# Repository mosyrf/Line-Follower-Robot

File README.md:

# Line-Follower-Robot
It was my first-year project as an electrical engineering student, to build a robot that could follow black or white lines. It wasn't a special line follower robot; it was designed to gain experience in project-based learning as a beginner.

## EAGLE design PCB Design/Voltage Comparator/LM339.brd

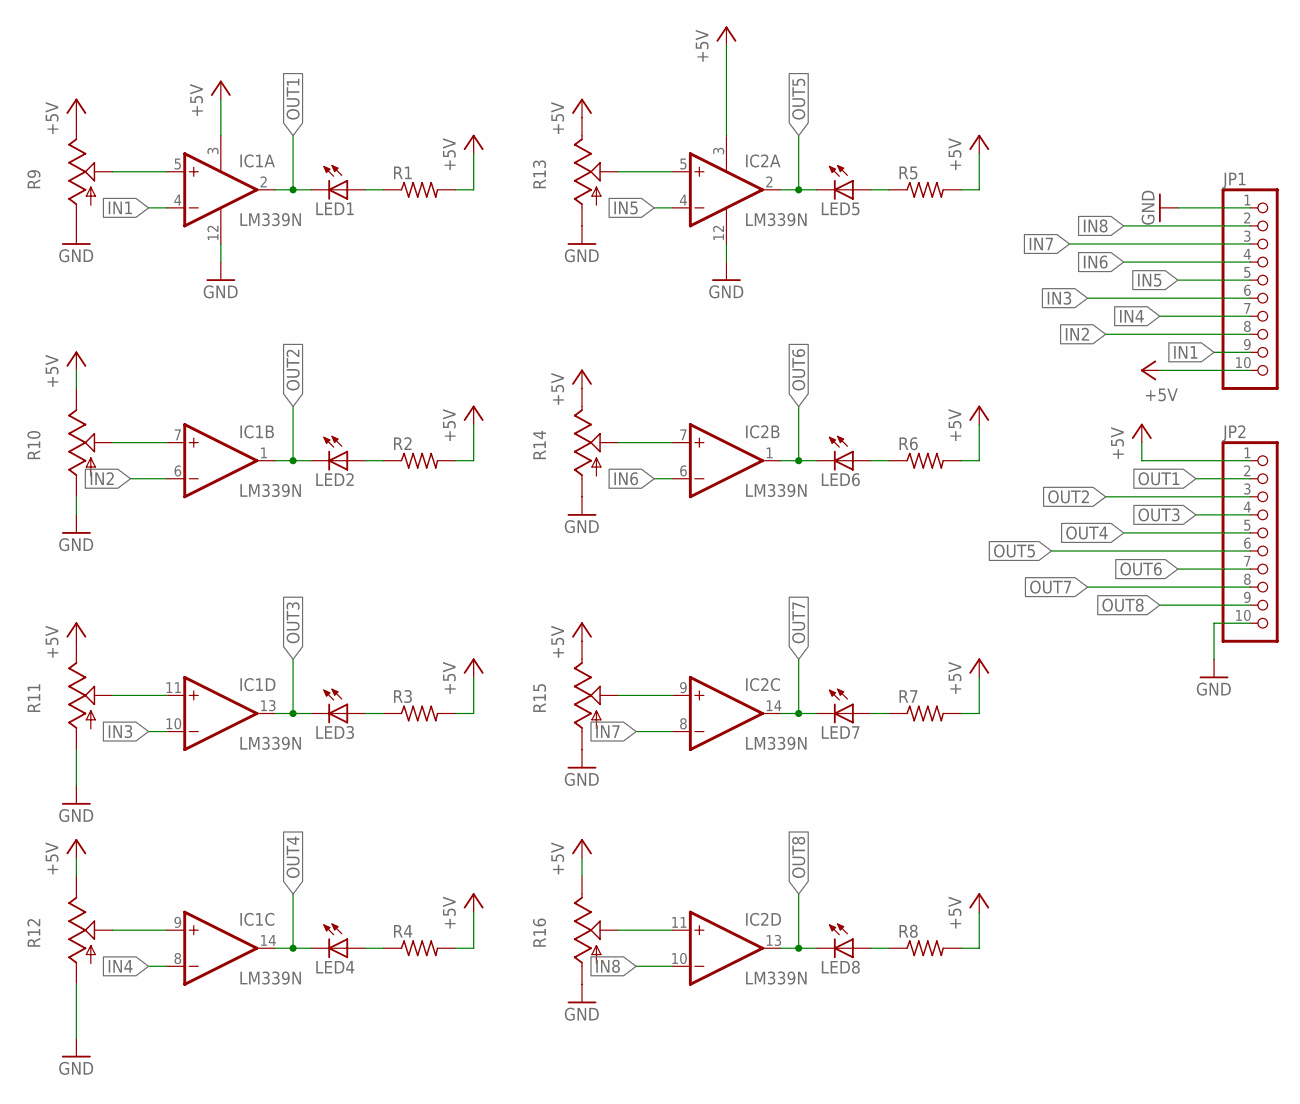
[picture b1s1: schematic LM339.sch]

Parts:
IC1, IC2: LM339N; DIL14
JP1, JP2: PINHD-1X10; 1X10
LED1, LED2, LED3, LED4, LED5, LED6, LED7, LED8: LED5MM
R1, R2, R3, R4, R5, R6, R7, R8: R-US_0204/7; 0204/7
R9, R10, R11, R12, R13, R14, R15, R16: TRIM_US-B25P; B25P

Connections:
+5V: IC1.3 (V+), IC2.3 (V+), JP1.10, JP2.1, R1.2, R2.2, R3.2, R4.2, R5.2, R6.2, R7.2, R8.2, R9.E, R10.E, R11.E, R12.E, R13.E, R14.E, R15.E, R16.E
GND: IC1.12 (GND), IC2.12 (GND), JP1.1, JP2.10, R9.A, R10.A, R11.A, R12.A, R13.A, R14.A, R15.A, R16.A
IN1: IC1.4 (-IN), JP1.9
IN2: IC1.6 (-IN), JP1.8
IN3: IC1.10 (-IN), JP1.6
IN4: IC1.8 (-IN), JP1.7
IN5: IC2.4 (-IN), JP1.5
IN6: IC2.6 (-IN), JP1.4
IN7: IC2.8 (-IN), JP1.3
IN8: IC2.10 (-IN), JP1.2
unnamed: LED2.A, R2.1
unnamed: LED1.A, R1.1
unnamed: LED3.A, R3.1
unnamed: LED4.A, R4.1
unnamed: LED5.A, R5.1
unnamed: LED6.A, R6.1
unnamed: LED7.A, R7.1
unnamed: LED8.A, R8.1
unnamed: IC1.11 (+IN), R11.S
unnamed: IC1.5 (+IN), R9.S
unnamed: IC1.7 (+IN), R10.S
unnamed: IC1.9 (+IN), R12.S
unnamed: IC2.9 (+IN), R15.S
unnamed: IC2.5 (+IN), R13.S
unnamed: IC2.7 (+IN), R14.S
unnamed: IC2.11 (+IN), R16.S
OUT1: IC1.2 (OUT), JP2.2, LED1.K (C)
OUT2: IC1.1 (OUT), JP2.3, LED2.K (C)
OUT3: IC1.13 (OUT), JP2.4, LED3.K (C)
OUT4: IC1.14 (OUT), JP2.5, LED4.K (C)
OUT5: IC2.2 (OUT), JP2.6, LED5.K (C)
OUT6: IC2.1 (OUT), JP2.7, LED6.K (C)
OUT7: IC2.14 (OUT), JP2.8, LED7.K (C)
OUT8: IC2.13 (OUT), JP2.9, LED8.K (C)

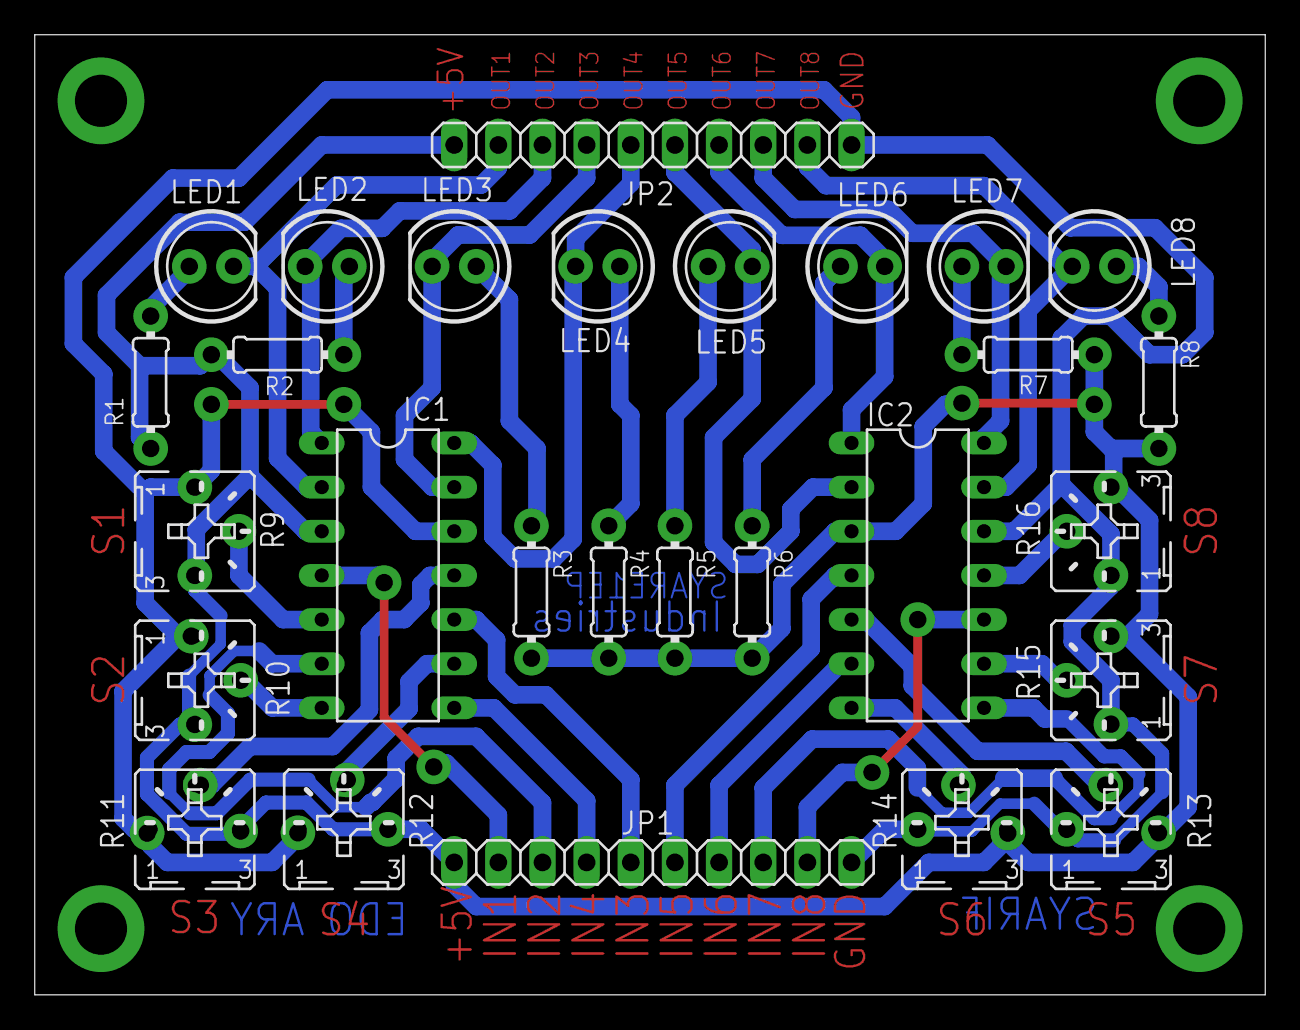
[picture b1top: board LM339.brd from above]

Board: 2 copper layers, 70.8 x 55.2 mm, 28 parts (0 on the bottom side), 34 nets.

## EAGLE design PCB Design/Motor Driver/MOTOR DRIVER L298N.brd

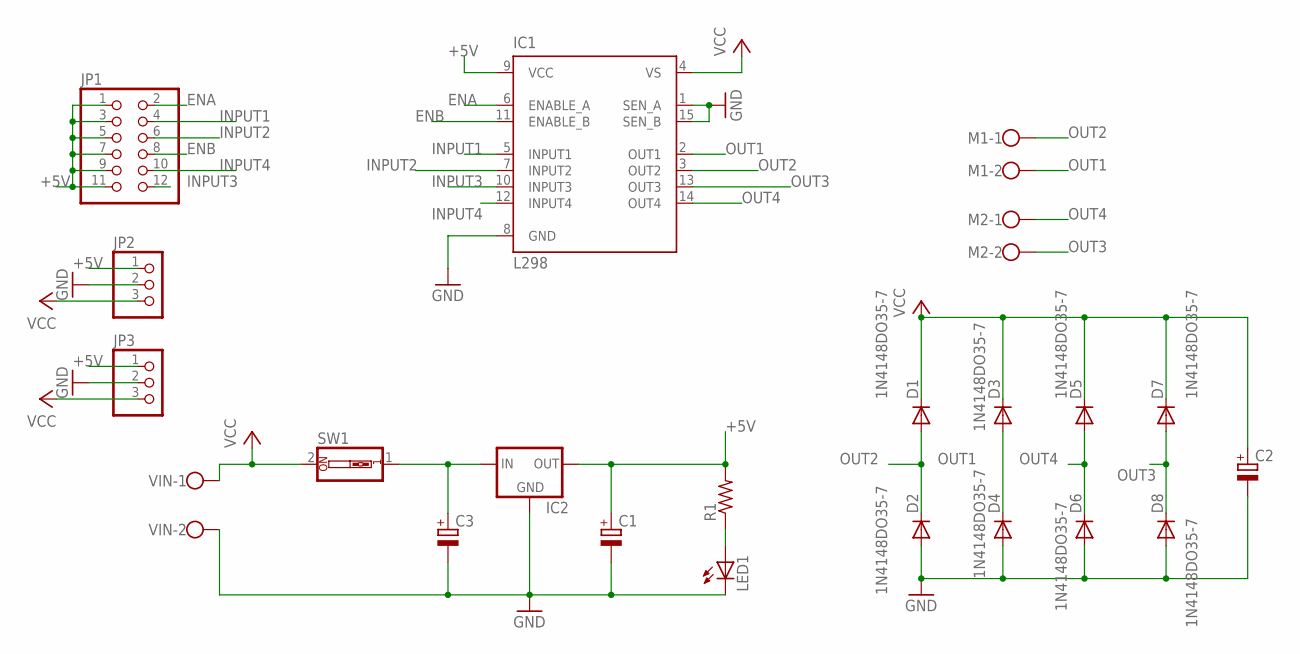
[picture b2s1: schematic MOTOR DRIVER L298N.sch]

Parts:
C1, C2, C3: CPOL-EUE5-6; E5-6
D1, D2, D3, D4, D5, D6, D7, D8: 1N4148DO35-7; DO35-7
IC1: L298; MULTIWATT-15
IC2: 78MXXS
JP1: PINHD-2X6; 2X06
JP2, JP3: PINHD-1X3; 1X03
LED1: LED5MM
M1, M2: W237-102
R1: R-US_0204/7; 0204/7
SW1: SW_DIP-1; EDG-01
VIN: W237-102

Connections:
+5V: C1.+, IC1.9 (VCC), IC2.OUT, JP1.1, JP1.3, JP1.5, JP1.7, JP1.9, JP1.11, JP2.1, JP3.1, R1.2
ENA: IC1.6 (ENABLE_A), JP1.2
ENB: IC1.11 (ENABLE_B), JP1.8
GND: C1.-, C2.-, C3.-, D2.A, D4.A, D6.A, D8.A, IC1.1 (SEN_A), IC1.8 (GND), IC1.15 (SEN_B), IC2.GND, JP2.2, JP3.2, LED1.K (C), VIN.2
INPUT1: IC1.5 (INPUT1), JP1.4
INPUT2: IC1.7 (INPUT2), JP1.6
INPUT3: IC1.10 (INPUT3), JP1.12
INPUT4: IC1.12 (INPUT4), JP1.10
unnamed: LED1.A, R1.1
unnamed: C3.+, IC2.IN, SW1.1
OUT1: D3.A, D4.C, IC1.2 (OUT1), M1.2
OUT2: D1.A, D2.C, IC1.3 (OUT2), M1.1
OUT3: D7.A, D8.C, IC1.13 (OUT3), M2.2
OUT4: D5.A, D6.C, IC1.14 (OUT4), M2.1
VCC: C2.+, D1.C, D3.C, D5.C, D7.C, IC1.4 (VS), JP2.3, JP3.3, SW1.2, VIN.1

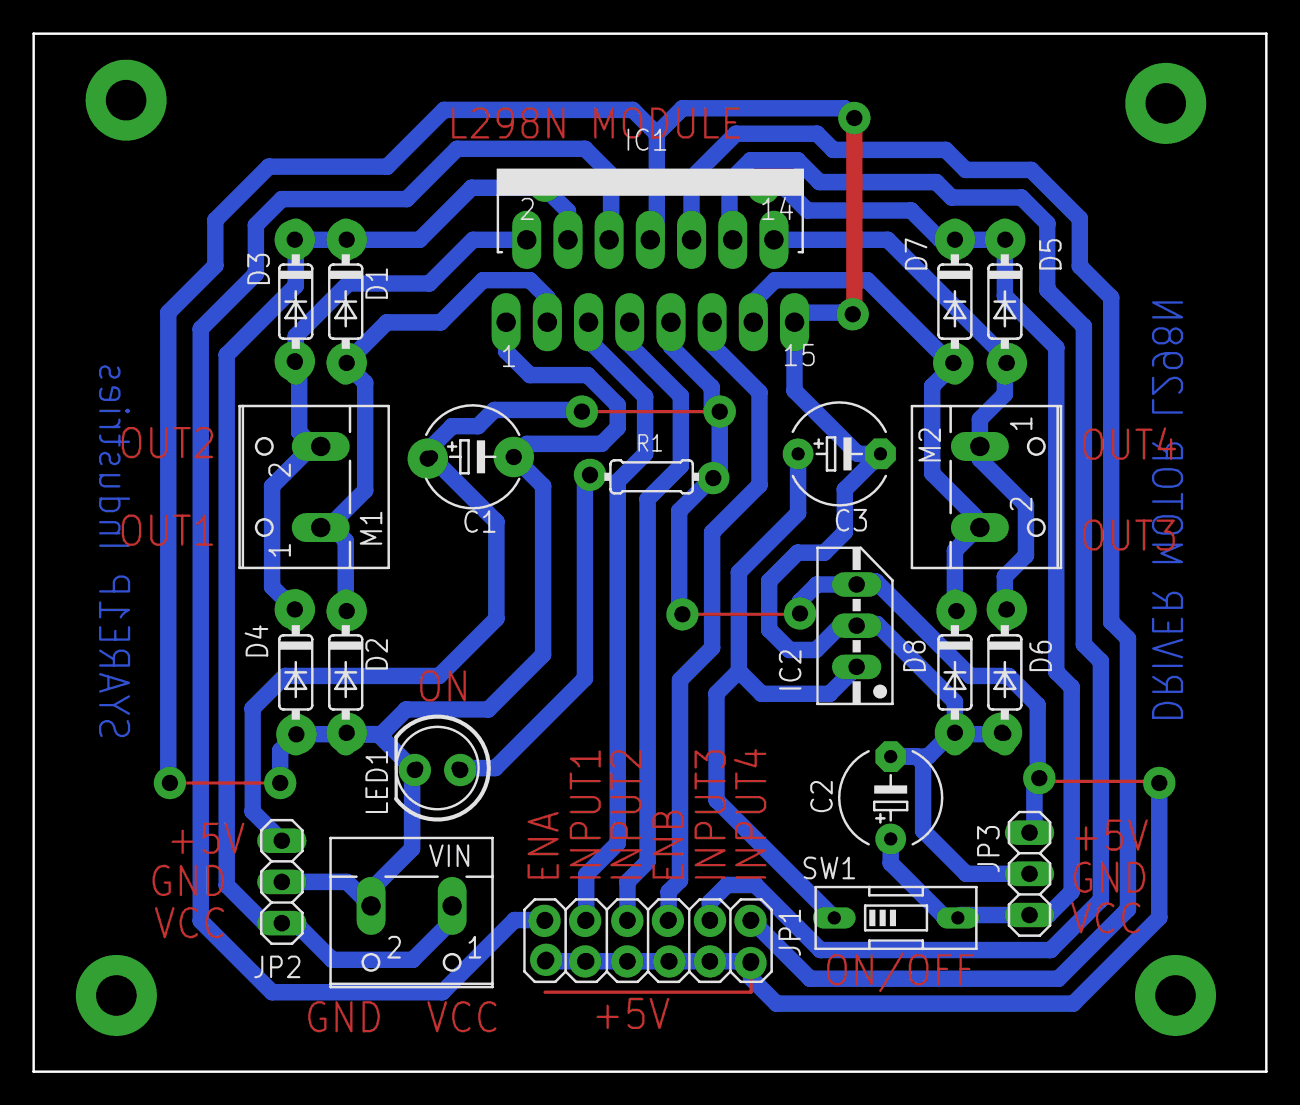
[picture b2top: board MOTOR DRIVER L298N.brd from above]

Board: 2 copper layers, 76.0 x 64.0 mm, 22 parts (0 on the bottom side), 15 nets.

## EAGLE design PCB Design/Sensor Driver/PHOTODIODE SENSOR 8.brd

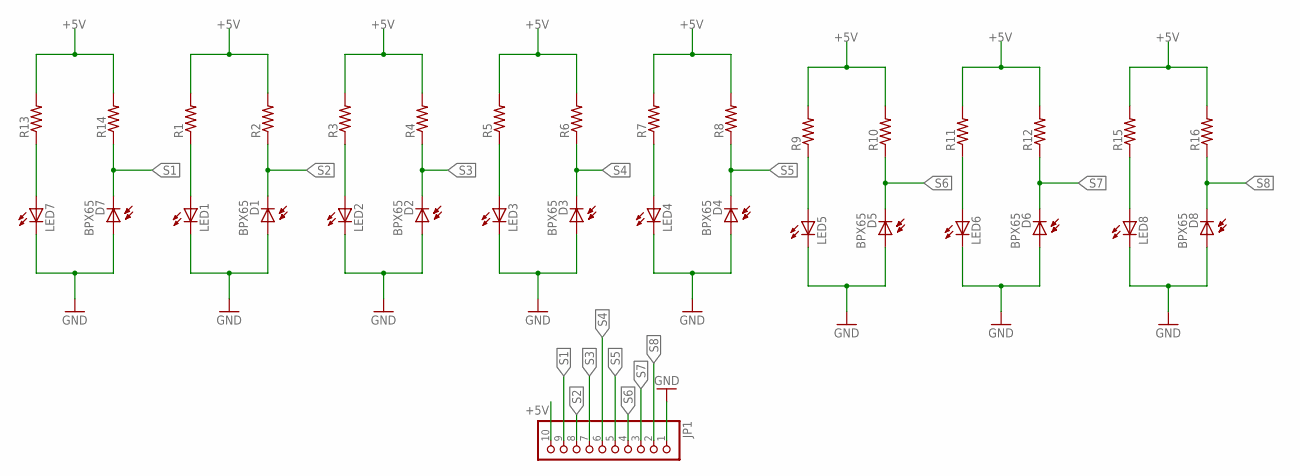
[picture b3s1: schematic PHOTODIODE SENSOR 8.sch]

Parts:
D1, D2, D3, D4, D5, D6, D7, D8: BPX65
JP1: PINHD-1X10; 1X10
LED1, LED2, LED3, LED4, LED5, LED6, LED7, LED8: LED5MM
R1, R2, R3, R4, R5, R6, R7, R8, R9, R10, R11, R12, R13, R14, R15, R16: R-US_0204/7; 0204/7

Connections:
+5V: JP1.10, R1.2, R2.2, R3.2, R4.2, R5.2, R6.2, R7.2, R8.2, R9.2, R10.2, R11.2, R12.2, R13.2, R14.2, R15.2, R16.2
GND: D1.A, D2.A, D3.A, D4.A, D5.A, D6.A, D7.A, D8.A, JP1.1, LED1.K (C), LED2.K (C), LED3.K (C), LED4.K (C), LED5.K (C), LED6.K (C), LED7.K (C), LED8.K (C)
unnamed: LED2.A, R3.1
unnamed: LED3.A, R5.1
unnamed: LED1.A, R1.1
unnamed: LED4.A, R7.1
unnamed: LED5.A, R9.1
unnamed: LED6.A, R11.1
unnamed: LED7.A, R13.1
unnamed: LED8.A, R15.1
S1: D7.K (C), JP1.9, R14.1
S2: D1.K (C), JP1.8, R2.1
S3: D2.K (C), JP1.7, R4.1
S4: D3.K (C), JP1.6, R6.1
S5: D4.K (C), JP1.5, R8.1
S6: D5.K (C), JP1.4, R10.1
S7: D6.K (C), JP1.3, R12.1
S8: D8.K (C), JP1.2, R16.1

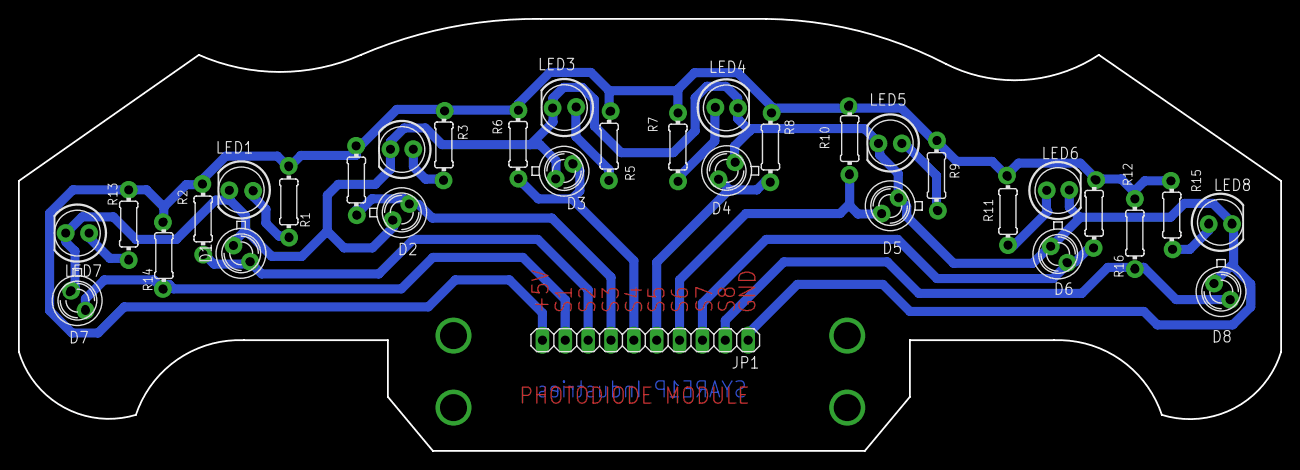
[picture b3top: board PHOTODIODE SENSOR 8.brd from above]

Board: 2 copper layers, 140.2 x 48.0 mm, 33 parts (0 on the bottom side), 18 nets.

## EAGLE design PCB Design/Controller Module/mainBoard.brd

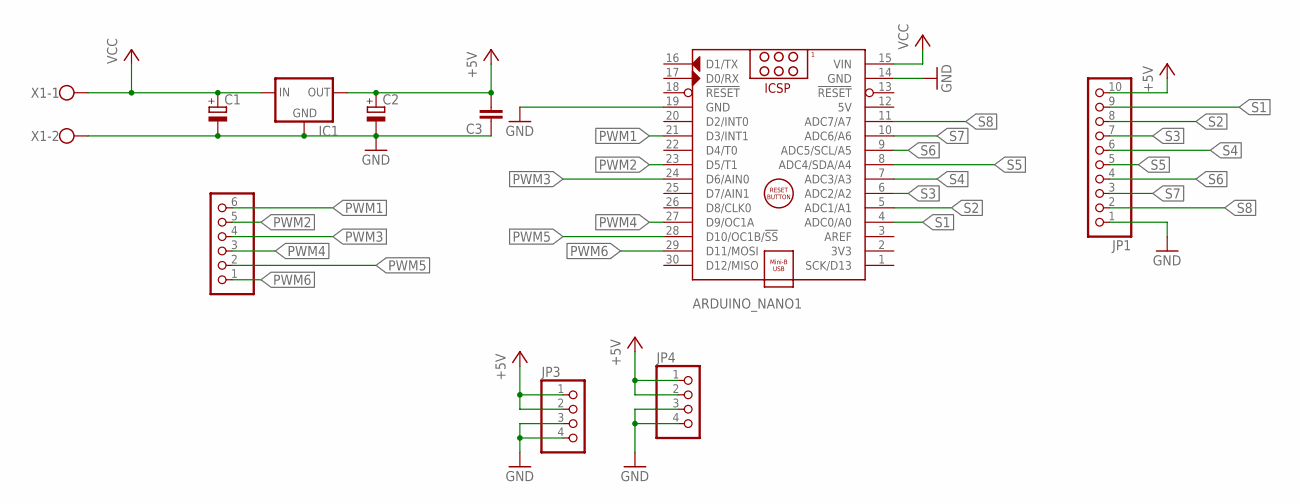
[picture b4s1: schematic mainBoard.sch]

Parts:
ARDUINO_NANO1: ARDUINO_NANO
C1, C2: CPOL-EUE2-5; E2-5
C3: C-EU050-025X075; C050-025X075
IC1: 78MXXS
JP1: PINHD-1X10; 1X10
JP2: PINHD-1X6; 1X06
JP3, JP4: PINHD-1X4; 1X04
X1: W237-102

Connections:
5V: ARDUINO_NANO1.12 (5V)
+5V: C2.+, C3.2, IC1.OUT, JP1.10, JP3.1, JP3.2, JP4.1, JP4.2
GND: ARDUINO_NANO1.14 (GND), ARDUINO_NANO1.19 (GND), C1.-, C2.-, C3.1, IC1.GND, JP1.1, JP3.3, JP3.4, JP4.3, JP4.4, X1.2
PWM1: ARDUINO_NANO1.21 (D3/INT1), JP2.6
PWM2: ARDUINO_NANO1.23 (D5/T1), JP2.5
PWM3: ARDUINO_NANO1.24 (D6/AIN0), JP2.4
PWM4: ARDUINO_NANO1.27 (D9/OC1A), JP2.3
PWM5: ARDUINO_NANO1.28 (D10/OC1B/!SS), JP2.2
PWM6: ARDUINO_NANO1.29 (D11/MOSI), JP2.1
S1: ARDUINO_NANO1.4 (ADC0/A0), JP1.9
S2: ARDUINO_NANO1.5 (ADC1/A1), JP1.8
S3: ARDUINO_NANO1.6 (ADC2/A2), JP1.7
S4: ARDUINO_NANO1.7 (ADC3/A3), JP1.6
S5: ARDUINO_NANO1.8 (ADC4/SDA/A4), JP1.5
S6: ARDUINO_NANO1.9 (ADC5/SCL/A5), JP1.4
S7: ARDUINO_NANO1.10 (ADC6/A6), JP1.3
S8: ARDUINO_NANO1.11 (ADC7/A7), JP1.2
VCC: ARDUINO_NANO1.15 (VIN), C1.+, IC1.IN, X1.1

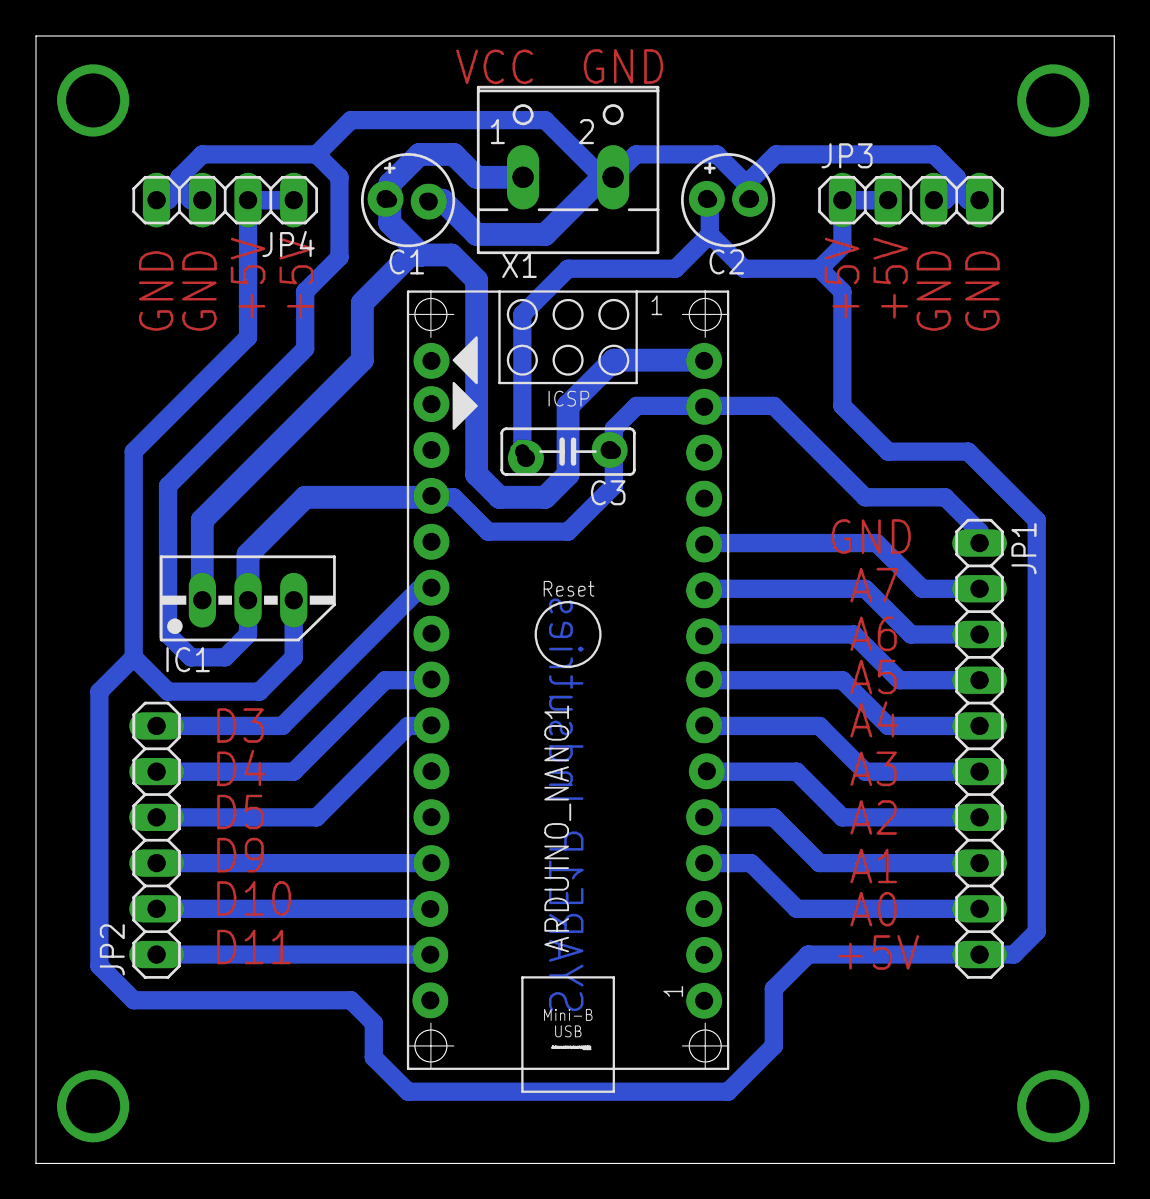
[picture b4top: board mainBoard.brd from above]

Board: 2 copper layers, 59.9 x 62.6 mm, 10 parts (0 on the bottom side), 17 nets.

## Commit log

2025-08-31 initial files related to PCB design
    Contains a brief explanation regarding the brief specifications of the PCB to be made.
2025-08-31 Create tes
2025-08-31 eagle file for controller
2025-08-31 eagle file for driver sensor
    contains 2 design versions with 6 and 8 sensors
2025-08-31 Create t
2025-08-31 eagle file for motor driver
2025-08-31 eagle file for voltage comparator
    v1 and v3 there are slight changes in the type of potentiometer used
2025-08-31 Create arduino program
2025-08-31 Create arduino program for testing driver motors
